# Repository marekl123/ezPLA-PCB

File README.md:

# ezPLA

C64 PLA replacement based on Altera EPM7032 CPLD chip.

For more information check: https://ezcontents.org/commodore-64-pla-chip-replacement
Tests (includes video): https://ezcontents.org/commodore-64-custom-pla-chip-test

To load the custom symbols and footprints correctly you can edit the files: fp-lib-table and sym-lib-table and change the working directory before loading the project inside KiCad. Or (if you are using Windows) you can also place the project files inside: C:/Projects/KiCAD/ezPLA/

License: CC-BY-SA https://creativecommons.org/licenses/by-sa/4.0/

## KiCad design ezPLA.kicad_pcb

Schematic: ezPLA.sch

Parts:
J1: JTAG-10; IDC-Header_2x05_P2.54mm_Custom
J2: Power; PinHeader_1x02_P2.54mm_Vertical
J3: PLA-headers; DIP-28_W15.24mm_mirrored
U2: EPM7032; PLCC-44_THT-Socket

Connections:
A12: J3.27, U2.40 (IO)
A13: J3.2, U2.9 (IO)
A14: J3.3, U2.11 (IO)
A15: J3.4, U2.17 (IO)
AEC: J3.25, U2.1 (IN)
BA: J3.26, U2.41 (IO)
BASIC: J3.17, U2.33 (IO)
CAS: J3.9, U2.24 (IO)
CASRAM: J3.18, U2.36 (IO)
CHAREN: J3.6, U2.20 (IO)
CHAROM: J3.15, U2.31 (IO)
EXROM: J3.23, U2.5 (IO)
GAME: J3.22, U2.6 (IO)
GND: J1.2 (GND), J1.10 (GND), J2.2, J3.14, U2.10 (GND), U2.22 (GND), U2.30 (GND), U2.42 (GND)
GRW: J3.13, U2.29 (IO)
HIRAM: J3.7, U2.21 (IO)
IO: J3.12, U2.28 (IO)
KERNAL: J3.16, U2.34 (IO)
LORAM: J3.8, U2.25 (IO)
NC1: J3.1, U2.8 (IO)
OE: J3.19, U2.37 (IO)
ROMH: J3.10, U2.26 (IO)
ROML: J3.11, U2.27 (IO)
RW: J3.24, U2.4 (IO)
TCK: J1.1 (TCK), U2.32 (IO)
TDI: J1.9 (TDI), U2.7 (IO)
TDO: J1.3 (TDO), U2.38 (IO)
TMS: J1.5 (TMS), U2.13 (IO)
VA12: J3.20, U2.39 (IO)
VA13: J3.21, U2.44 (IN)
VA14: J3.5, U2.18 (IO)
VCC: J1.4 (VREF), J2.1, J3.28, U2.3 (VCC), U2.15 (VCC), U2.23 (VCC), U2.35 (VCC)

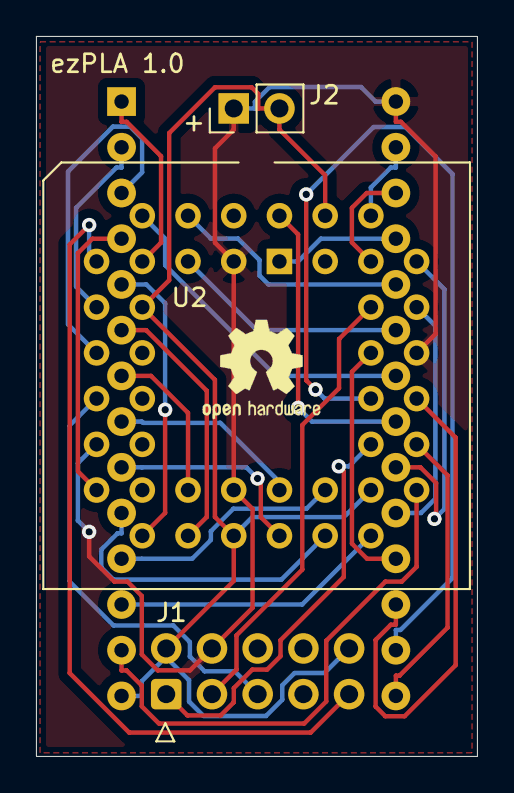
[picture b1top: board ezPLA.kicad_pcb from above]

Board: 2 copper layers, 24.5 x 40.0 mm, 4 parts (1 on the bottom side), 32 nets.

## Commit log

2021-09-02 Update KiCad files

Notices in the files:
ezPLA.kicad_pcb:
ezContents - CC-BY-SA 2021
